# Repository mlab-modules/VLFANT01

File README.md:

<!--- Name:VLFANT01B: --->
# VLFANT01B
<!--- LongName --->
## VLF antenna interconnection module
<!--- ELongName --->

<!--- Lead --->

<!--- ELead --->

The module is usually used to make a magnetic loop antenna from the UTP pigtail. It is basic antenna for [VLF ionospheric monitoring station](https://github.com/Ionozor/VLFMON01).

<!--- Description --->
<!--- EDescription --->
<!--- Content --->

## Hardware

The module could be used by multiple ways

### Antenna feed end on MLAB board

This usage case uses only one RJ45 connector populated on board. This connector is used for connection the UTP feed from the antenna.

### Antenna connection module

In that situation all three RJ45 connectors are populated on the board. The two are used for connection the antenna loop. The last is used for feeding the signal to the receiver unit.

## VLF antenna construction

The antenna is made from an aluminium tube ring. The parameters of the aluminium tube are not critical. But it is practical to use an tube which allows direct insertion of UTP pigtail including the connectors.
The circumference of the tube ring should match the lengh of UTP cable used. Therefore the example 1.5m circle diameter aproximately match to 5m lenght UTP cable pigtail. In the reality we used the STP (Shilded variant of UTP cable), to minimize possibility of differences between antennas by different shaping of the cable in the tube, which could alter overall capacity, resulting in different resonant frequency. 

<!--- EContent --->
<sub><sup> Generated with [MLABweb](https://github.com/MLAB-project/MLABweb). (2019-09-12)</sup></sub>

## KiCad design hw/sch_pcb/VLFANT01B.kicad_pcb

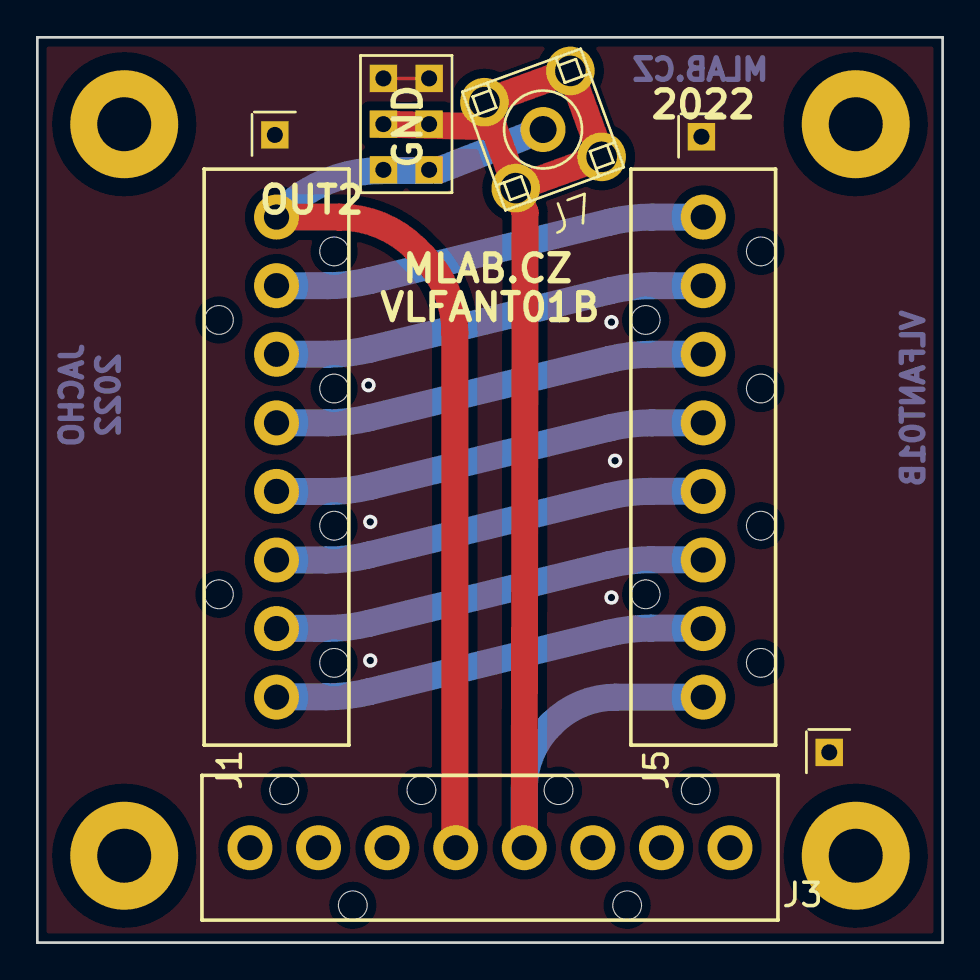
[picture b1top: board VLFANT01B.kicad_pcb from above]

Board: 2 copper layers, 50.3 x 50.3 mm, 12 parts (0 on the bottom side), 10 nets.

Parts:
J1, J3, J5: IDC381-8-110
J2, J4, J6: JUMP_2x1; Straight_1x01
J7: SMA; SMA6251A13G50
J8: JUMP_3X2; Straight_2x03
M1, M2, M3, M4: HOLE; MountingHole_3mm

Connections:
/OUT1: J1.1, J3.4, J7.1, J8.1 (2), J8.2
/OUT2: J3.5, J5.8, J7.2, J8.3 (4), J8.4
GND: J2.1, J4.1, J6.1, J8.5 (6), J8.6
unnamed: J1.2, J5.1
unnamed: J1.3, J5.2
unnamed: J1.4, J5.3
unnamed: J1.5, J5.4
unnamed: J1.6, J5.5
unnamed: J1.7, J5.6
unnamed: J1.8, J5.7

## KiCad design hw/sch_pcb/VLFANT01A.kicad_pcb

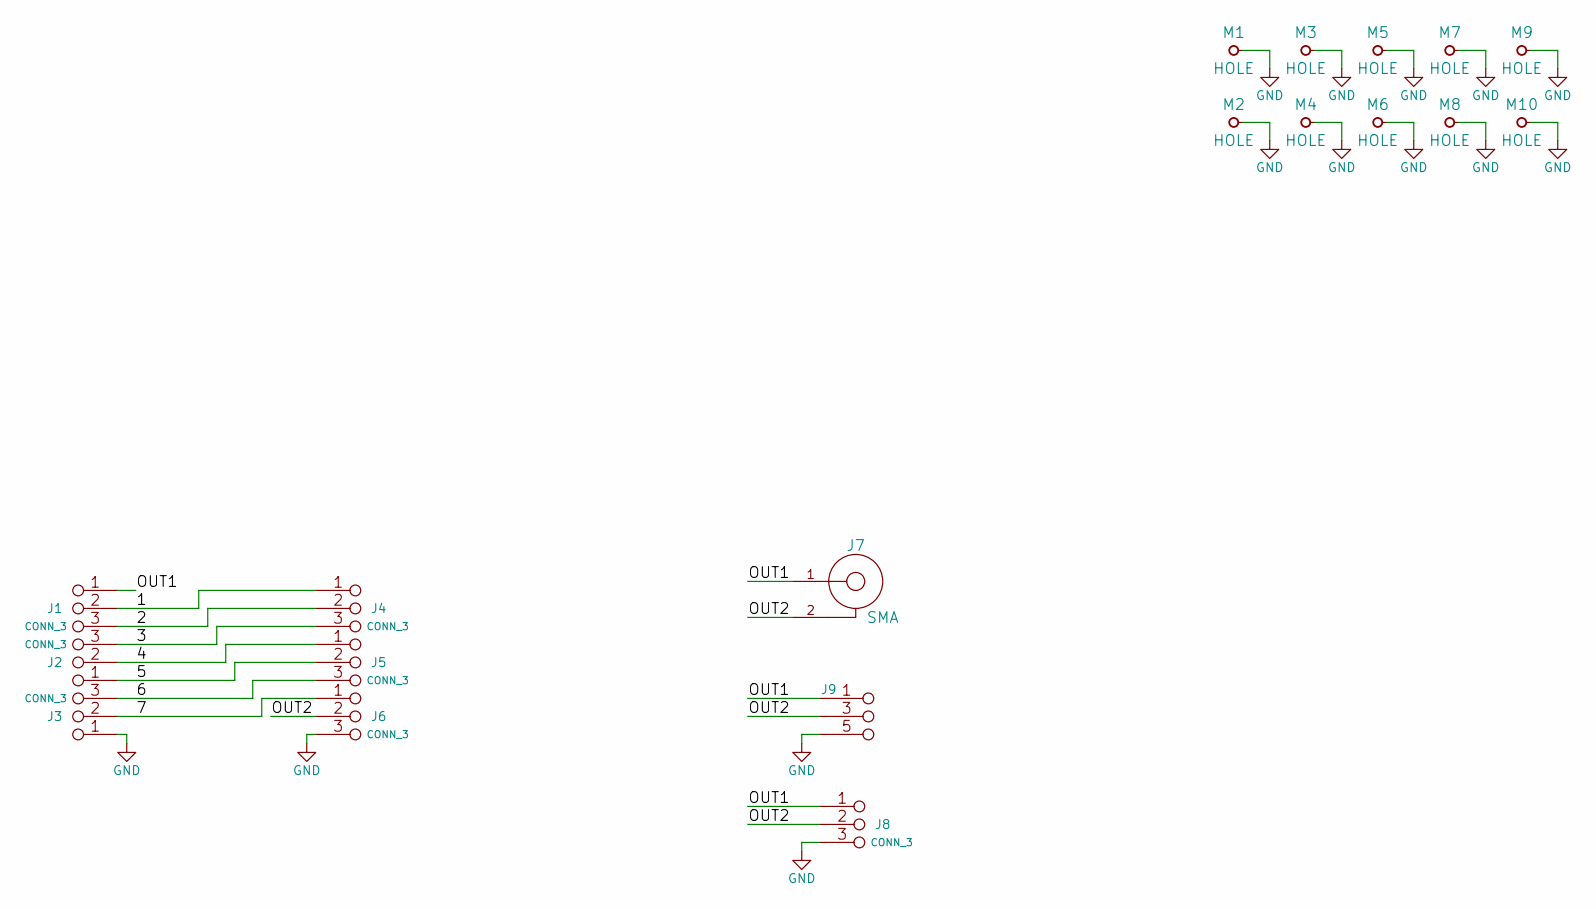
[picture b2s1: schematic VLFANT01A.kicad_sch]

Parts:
J1, J2, J3, J4, J5, J6, J8: CONN_3; AVX_009175003001006
J7: SMA; SMA6251A13G50
J9: JUMP_3X2; Straight_2x03
M1, M2, M3, M4, M5, M6, M7, M8, M9, M10: HOLE; MountingHole_3mm

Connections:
/1: J1.2 (PM), J4.1
/2: J1.3, J4.2 (PM)
/3: J2.3, J4.3
/4: J2.2 (PM), J5.1
/5: J2.1, J5.2 (PM)
/6: J3.3, J5.3
/7: J3.2 (PM), J6.1
/OUT1: J1.1, J7.1, J8.1, J9.1 (2), J9.2
/OUT2: J6.2 (PM), J7.2, J8.2 (PM), J9.3 (4), J9.4
GND: J3.1, J6.3, J8.3, J9.5 (6), J9.6, M1.1, M2.1, M3.1, M4.1, M5.1, M6.1, M7.1, M8.1, M9.1, M10.1

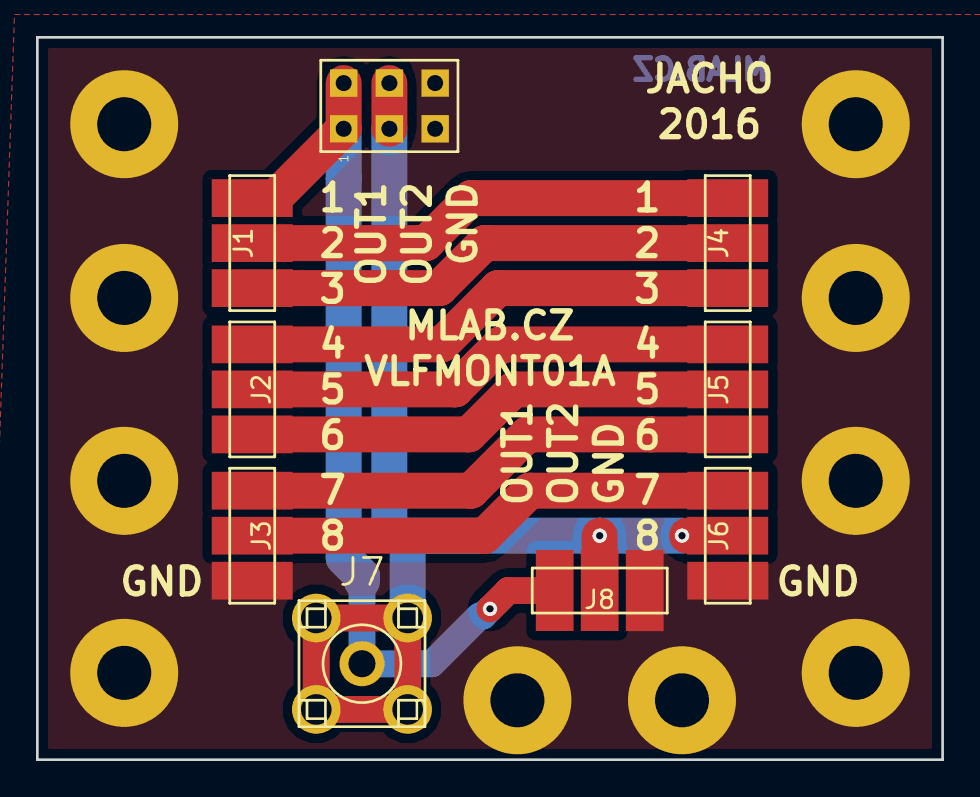
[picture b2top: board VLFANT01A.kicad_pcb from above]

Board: 2 copper layers, 50.3 x 40.1 mm, 19 parts (0 on the bottom side), 10 nets.

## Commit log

2019-09-11 Commiting module from VLFMON01A ionospheric monitoring station.
2019-09-12 Odebrani modulu nebot jej nelze primo pridat do databaze.
2019-09-12 [MLABweb] Documentation edits; VLFANT01A
2019-09-12 Pridani zdrojovych souboru po vytvoreni modulu v databazi.
2019-09-12 Odebrání modulu pro umožnění vytvoření modulu v databázi.
2019-09-12 [MLABweb] Documentation edits; VLFANT01B
2019-09-12 Vraceni zdrojových souborů po vytvoření modulu v databázi.
2021-07-17 Adding basic documentation to the antenna construction.
2022-01-26 Update project to new KiCAD 6 format. Regenerating the schematic PDF.
2022-04-06 automated commit; add github actions
2022-04-06 Update actions products
2022-05-15 actions
2022-05-15 add assets
2022-05-15 update to new kicad format
2022-05-15 verze s narazecimi konektory
2023-05-25 Update metadata files
2023-05-28 Update workflow files
2023-07-05 automated commit; rename source files to new naming convence
2023-09-16 Update image to image_title
2023-09-16 Update status
